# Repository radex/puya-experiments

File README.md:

# puya-experiments

Experimenting with very, very cheap microcontrollers - PY32 series by PUYA(普冉). STM32-like, Cortex M0, but cheaper!

## Breakout boards

Includes breakout board designs (KiCad 8 projects) for:

- py32f002af15p6tu - a $0.15 TSSOP-20 microcontroller
- PY32F003L24D6TR - a comparatively pricey ($0.29) but tiny 2x3mm DFN-8 microcontroller

| </a> | </a> |
| -- | -- |

## Resources and references

- https://github.com/IOsetting/py32f0-template
- https://github.com/wagiminator/Development-Boards
- https://www.cnx-software.com/2023/02/09/8-cents-for-an-arm-cortex-m0-microcontroller-meet-puya-py32-series-mcus/

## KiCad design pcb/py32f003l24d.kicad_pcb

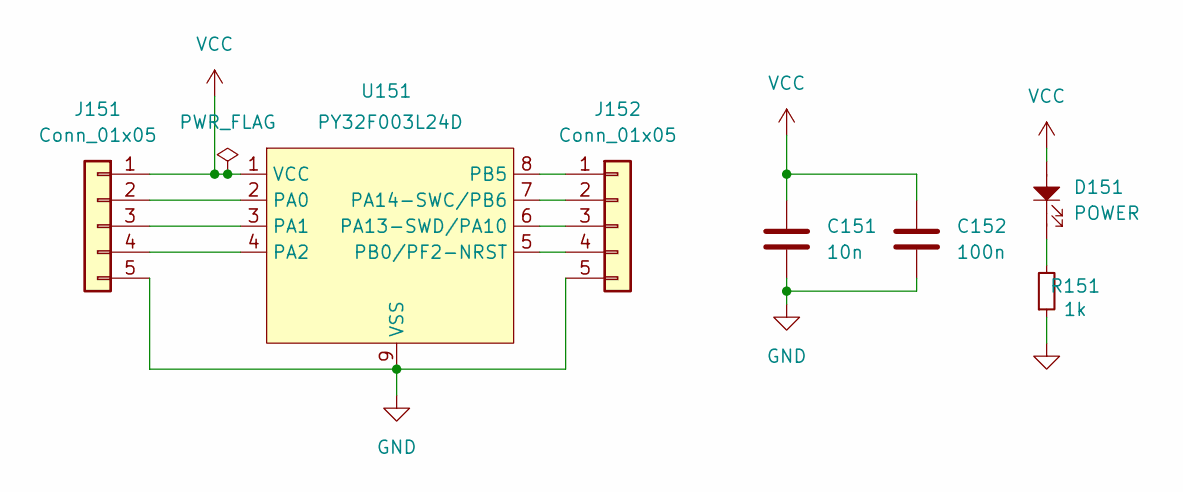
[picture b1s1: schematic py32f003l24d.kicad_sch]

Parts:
C151: 10n; C_0402_1005Metric; LCSC C15195
C152: 100n; C_0402_1005Metric; LCSC C1525
D151: POWER; LED_0603_1608Metric_Dot; LCSC C2286
J151, J152: Conn_01x05; PinHeader_1x05_P2.54mm_Vertical
R151: 1k; R_0402_1005Metric; LCSC C11702
U151: PY32F003L24D; DFN-8-1EP_3x2mm_P0.5mm_EP1.3x1.5mm; LCSC C5128436

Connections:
GND: C151.2, C152.2, J151.5, J152.5, R151.1, U151.9 (VSS)
unnamed: D151.1, R151.2
unnamed: J151.2, U151.2 (PA0)
unnamed: J151.3, U151.3 (PA1)
unnamed: J151.4, U151.4 (PA2)
unnamed: J152.1, U151.8 (PB5)
unnamed: J152.2, U151.7 (PA14-SWC/PB6)
unnamed: J152.3, U151.6 (PA13-SWD/PA10)
unnamed: J152.4, U151.5 (PB0/PF2-NRST)
VCC: C151.1, C152.1, D151.2, J151.1, U151.1 (VCC)

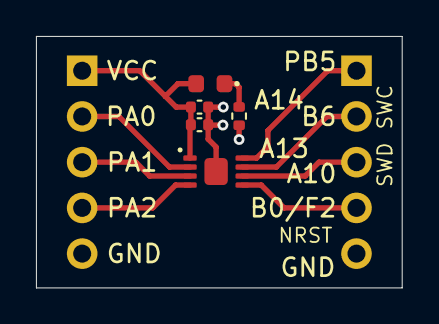
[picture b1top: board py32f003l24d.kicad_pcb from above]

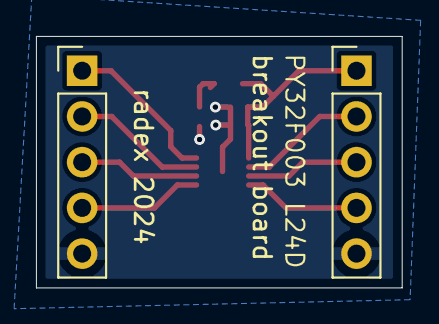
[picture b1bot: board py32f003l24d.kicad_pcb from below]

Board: 2 copper layers, 20.3 x 14.0 mm, 7 parts (2 on the bottom side), 10 nets.

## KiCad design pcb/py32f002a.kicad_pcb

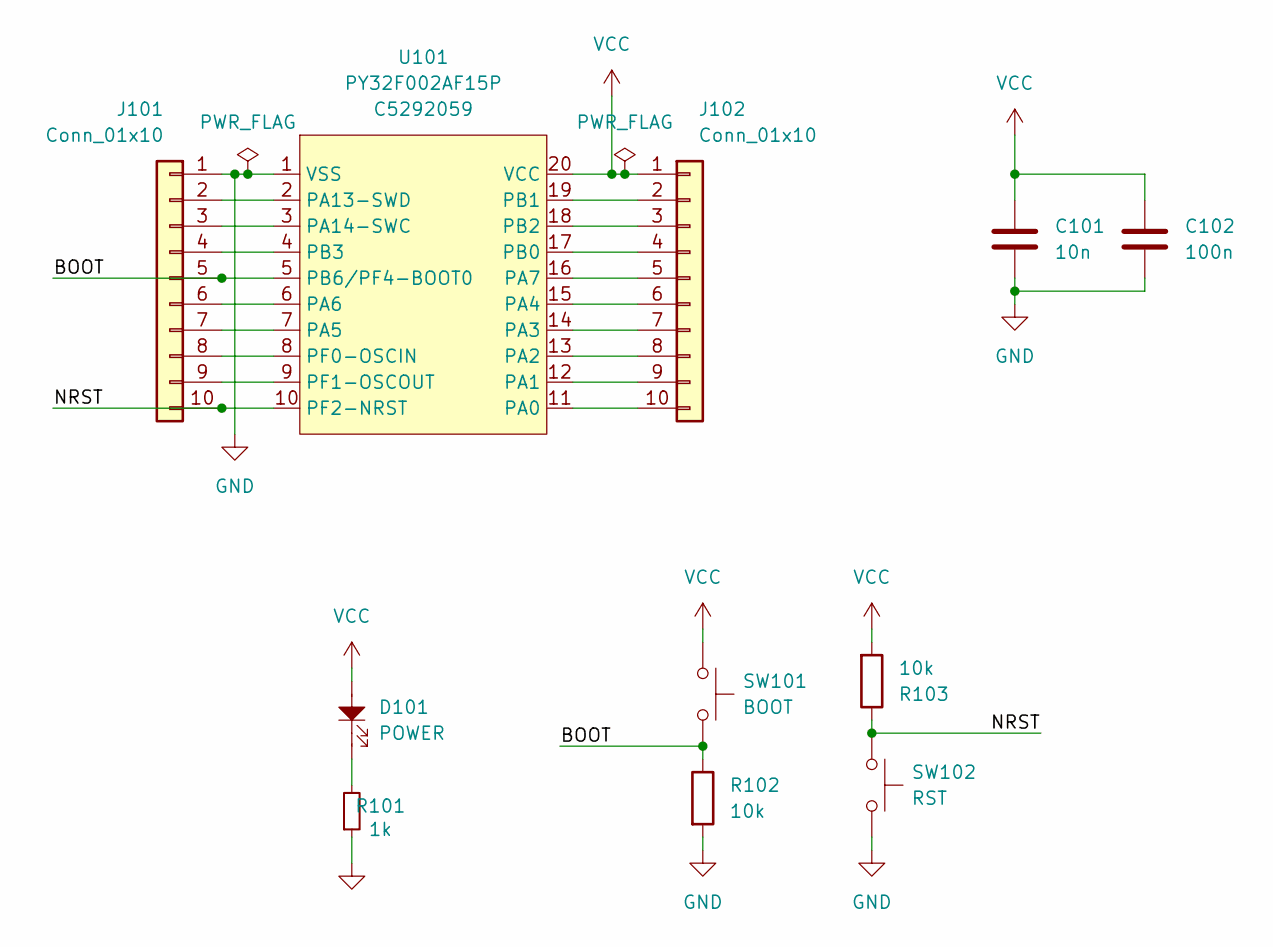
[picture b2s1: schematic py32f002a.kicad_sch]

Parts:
C101: 10n; C_0402_1005Metric; LCSC C15195
C102: 100n; C_0402_1005Metric; LCSC C1525
D101: POWER; LED_0603_1608Metric_Dot; LCSC C2286
J101, J102: Conn_01x10; PinHeader_1x10_P2.54mm_Vertical
R101: 1k; R_0402_1005Metric; LCSC C11702
R102, R103: 10k; R_0402_1005Metric; LCSC C25744
SW101: BOOT; TS-1187A-B-A-B; LCSC C318884
SW102: RST; TS-1187A-B-A-B; LCSC C318884
U101: PY32F002AF15P; TSSOP-20_4.4x6.5mm_P0.65mm; LCSC C5292059

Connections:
/BOOT: J101.5, R102.1, SW101.1, U101.5 (PB6/PF4-BOOT0)
/NRST: J101.10, R103.1, SW102.1, U101.10 (PF2-NRST)
GND: C101.2, C102.2, J101.1, R101.1, R102.2, SW102.2, U101.1 (VSS)
unnamed: D101.1, R101.2
unnamed: J101.2, U101.2 (PA13-SWD)
unnamed: J101.3, U101.3 (PA14-SWC)
unnamed: J101.4, U101.4 (PB3)
unnamed: J101.6, U101.6 (PA6)
unnamed: J101.7, U101.7 (PA5)
unnamed: J101.8, U101.8 (PF0-OSCIN)
unnamed: J101.9, U101.9 (PF1-OSCOUT)
unnamed: J102.2, U101.19 (PB1)
unnamed: J102.3, U101.18 (PB2)
unnamed: J102.4, U101.17 (PB0)
unnamed: J102.5, U101.16 (PA7)
unnamed: J102.6, U101.15 (PA4)
unnamed: J102.7, U101.14 (PA3)
unnamed: J102.8, U101.13 (PA2)
unnamed: J102.9, U101.12 (PA1)
unnamed: J102.10, U101.11 (PA0)
VCC: C101.1, C102.1, D101.2, J102.1, R103.2, SW101.2, U101.20 (VCC)

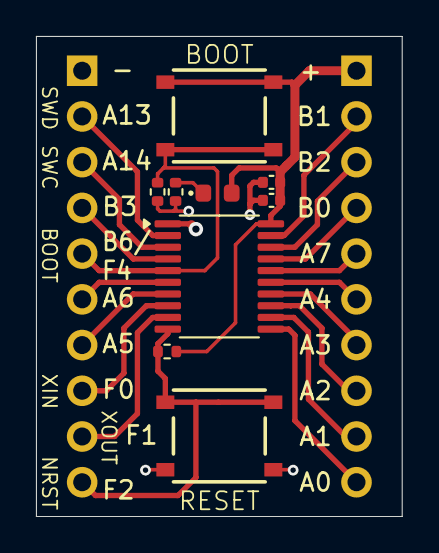
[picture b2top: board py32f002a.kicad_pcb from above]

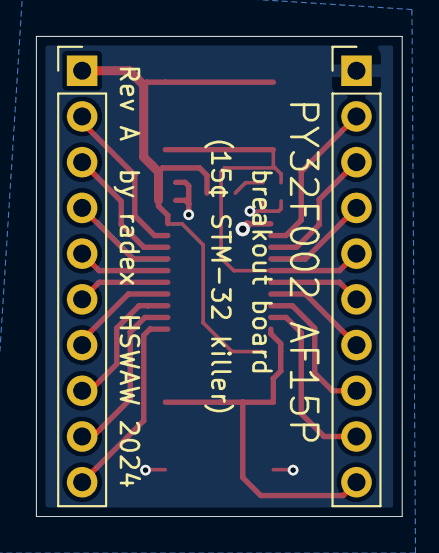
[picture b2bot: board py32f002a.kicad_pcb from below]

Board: 2 copper layers, 20.3 x 26.7 mm, 11 parts (2 on the bottom side), 21 nets.

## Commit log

2024-03-18 dump pcbs
2024-03-18 add readme
2024-03-18 tweaks
